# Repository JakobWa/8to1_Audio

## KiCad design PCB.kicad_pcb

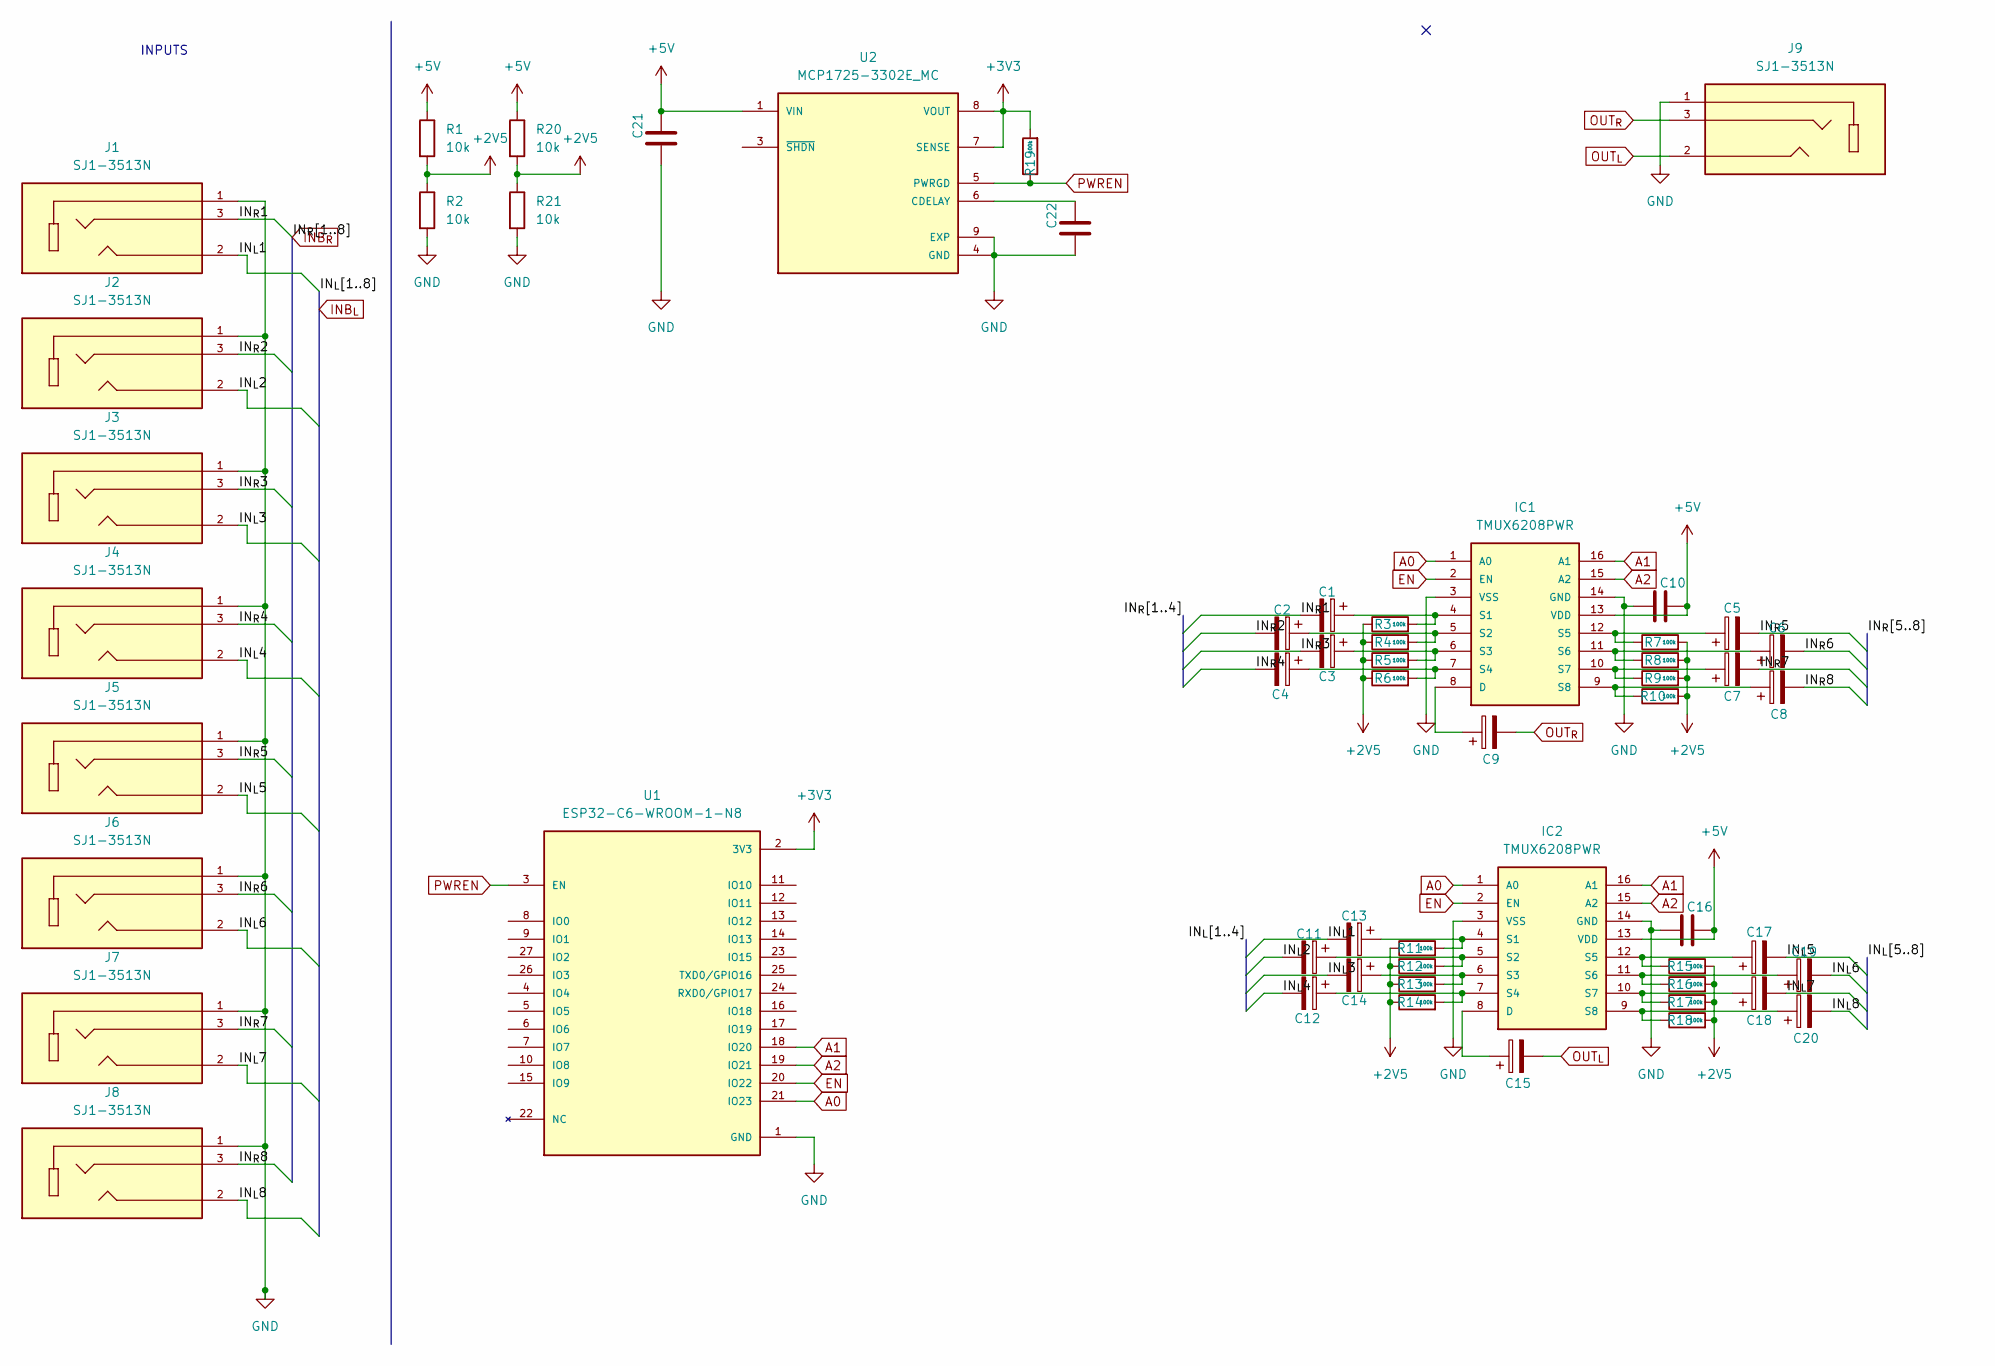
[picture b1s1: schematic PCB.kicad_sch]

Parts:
C1, C2, C3, C4, C5, C6, C7, C8, C9, C11, C12, C13, C14, C15, C17, C18, C19, C20: 4.7µF; CAPAE430X565N
C10, C16, C21: 4.7µF; C_0805_2012Metric
C22: 1000pF; C_0805_2012Metric
IC1, IC2: TMUX6208PWR; SOP65P640X120-16N; MOUSER_PART_NUMBER 595-TMUX6208PWR
J1, J2, J3, J4, J5, J6, J7, J8, J9: SJ1-3513N; CUI_SJ1-3513N; PARTREV 1.02
R1, R2, R20, R21: 10k; R_0805_2012Metric
R3, R4, R5, R6, R7, R8, R9, R10, R11, R12, R13, R14, R15, R16, R17, R18, R19: 100k; R_0805_2012Metric
U1: ESP32-C6-WROOM-1-N8; XCVR_ESP32-C6-WROOM-1-N8; PARTREV 1.0
U2: MCP1725-3302E_MC; SON50P200X300X100-9N; PARTREV B

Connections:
+2V5: R1.2, R2.1, R3.1, R4.1, R5.1, R6.1, R7.2, R8.2, R9.2, R10.2, R11.1, R12.1, R13.1, R14.1, R15.2, R16.2, R17.2, R18.2, R20.2, R21.1
+3V3: R19.2, U1.2 (3V3), U2.7 (SENSE), U2.8 (VOUT)
+5V: C10.2, C16.2, C21.2, IC1.13 (VDD), IC2.13 (VDD), R1.1, R20.1, U2.1 (VIN), U2.2 (VIN)
/IN_{L}1: C13.2, J1.2
/IN_{L}2: C11.2, J2.2
/IN_{L}3: C14.2, J3.2
/IN_{L}4: C12.2, J4.2
/IN_{L}5: C17.2, J5.2
/IN_{L}6: C19.2, J6.2
/IN_{L}7: C18.2, J7.2
/IN_{L}8: C20.2, J8.2
/IN_{R}1: C1.2, J1.3
/IN_{R}2: C2.2, J2.3
/IN_{R}3: C3.2, J3.3
/IN_{R}4: C4.2, J4.3
/IN_{R}5: C5.2, J5.3
/IN_{R}6: C6.2, J6.3
/IN_{R}7: C7.2, J7.3
/IN_{R}8: C8.2, J8.3
A0: IC1.1 (A0), IC2.1 (A0), U1.21 (IO23)
A1: IC1.16 (A1), IC2.16 (A1), U1.18 (IO20)
A2: IC1.15 (A2), IC2.15 (A2), U1.19 (IO21)
EN: IC1.2 (EN), IC2.2 (EN), U1.20 (IO22)
GND: C10.1, C16.1, C21.1, C22.1, IC1.3 (VSS), IC1.14 (GND), IC2.3 (VSS), IC2.14 (GND), J1.1, J2.1, J3.1, J4.1, J5.1, J6.1, J7.1, J8.1, J9.1, R2.2, R21.2, U1.1 (GND), U1.28 (GND), U1.29_1 (GND), U1.29_2 (GND), U1.29_3 (GND), U1.29_4 (GND), U1.29_5 (GND), U1.29_6 (GND), U1.29_7 (GND), U1.29_8 (GND), U1.29_9 (GND), U2.4 (GND), U2.9 (EXP)
unnamed: C9.1, IC1.8 (D)
unnamed: C1.1, IC1.4 (S1), R3.2
unnamed: C2.1, IC1.5 (S2), R4.2
unnamed: C3.1, IC1.6 (S3), R5.2
unnamed: C4.1, IC1.7 (S4), R6.2
unnamed: C5.1, IC1.12 (S5), R7.1
unnamed: C6.1, IC1.11 (S6), R8.1
unnamed: C7.1, IC1.10 (S7), R9.1
unnamed: C8.1, IC1.9 (S8), R10.1
unnamed: C15.1, IC2.8 (D)
unnamed: C13.1, IC2.4 (S1), R11.2
unnamed: C11.1, IC2.5 (S2), R12.2
unnamed: C14.1, IC2.6 (S3), R13.2
unnamed: C12.1, IC2.7 (S4), R14.2
unnamed: C17.1, IC2.12 (S5), R15.1
unnamed: C19.1, IC2.11 (S6), R16.1
unnamed: C18.1, IC2.10 (S7), R17.1
unnamed: C20.1, IC2.9 (S8), R18.1
unnamed: C22.2, U2.6 (CDELAY)
OUT_{L}: C15.2, J9.2
OUT_{R}: C9.2, J9.3
PWREN: R19.1, U1.3 (EN), U2.5 (PWRGD)

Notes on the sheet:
INPUTS

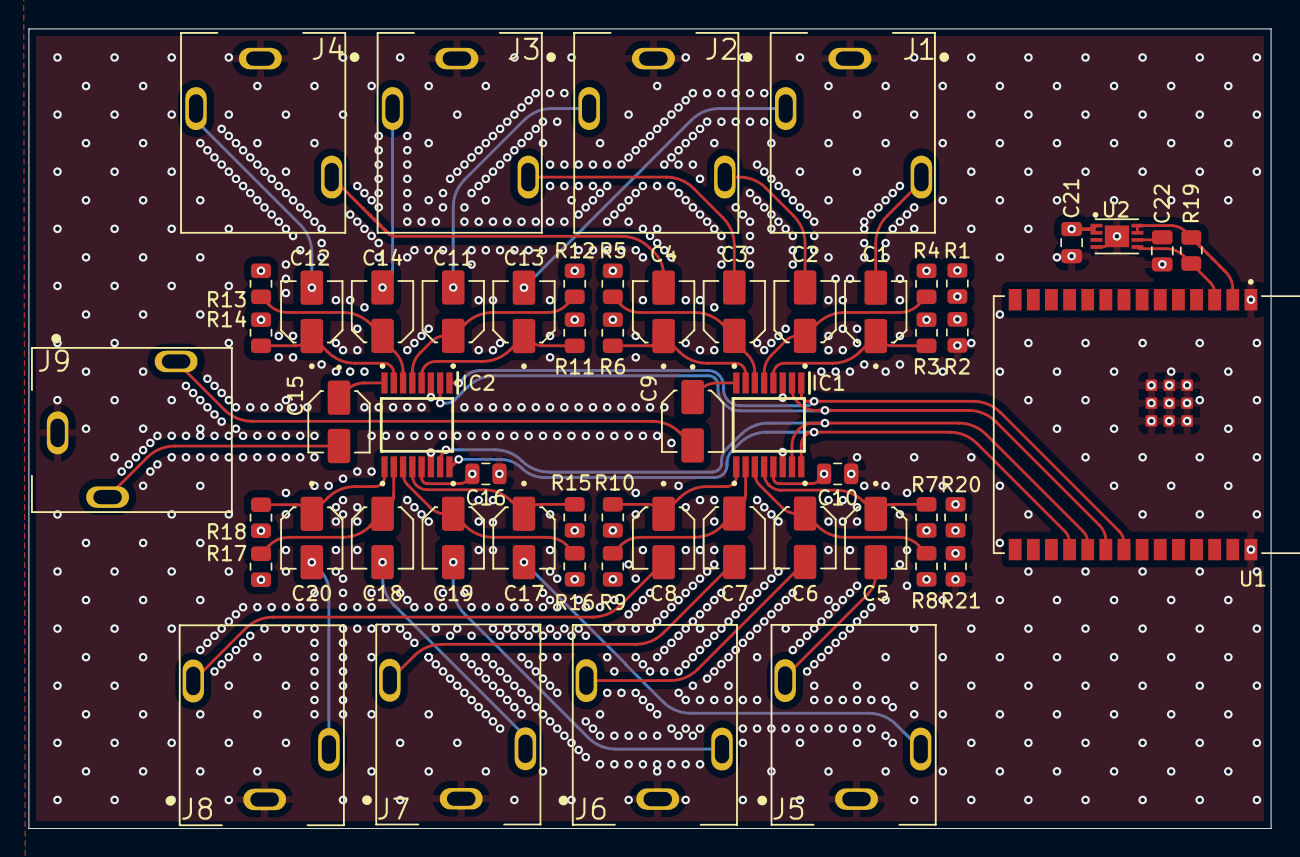
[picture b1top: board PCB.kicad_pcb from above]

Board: 4 copper layers, 87.0 x 56.0 mm, 56 parts (0 on the bottom side), 46 nets.

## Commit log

2026-01-03 initial
